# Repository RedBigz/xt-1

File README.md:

## IMPORTANT

- The JST PH connectors from the t-plugs to the supp. board need to have reverse connectors!

# XT-1

-green?style=for-the-badge)

A modular CoreXY 3D Printer with a focus on repairability.

| [READ THE JOURNAL](./JOURNAL.md) | [READ CAD CREDITS](CAD_CREDITS.md) |
| -------------------------------- | ---------------------------------- |

|  |                   |
| ---------------------------------------------------------------------- | ---------------------------------------------------------- |
|        |  |

## Who I am and why I made this

Hi, I'm May, a 15-year-old programmer and hardware enthusiast from Australia. I have spent the past few weeks developing a custom 3D printer based on the CoreXY motion system that allows for custom component bays to be inserted on the toolhead. I made this dovetail plug (t-plug) system to mimic the concept of [Framework](https://frame.work)'s laptop expansion bays. I believe expansion bays largely simplify repairs performed by consumers and allows for greater self-expression through custom designs that can be attached to the toolhead.

## What is this?

The XT-1 is a custom CoreXY 3D printer with two custom t-plug (as defined above) bays to transmit UART and 5V & 24V PWM signals for things such as:

- Accelerometers (not ADXL as they're SPI)
- Laser Diodes
- Fans

Here are some basic statistics for the printer:

- 2 t-plug bays
- 2WD CoreXY System
- 180x180x160 build volume
- ~360x360x420 external dimensions

# Gallery

## CAD Model

## Supplementary Board

## T-Plug

# Building

## CAD Models

To export parts, open the model in OnShape [here](https://cad.onshape.com/documents/9bd0c3164ed27c6437ee23ee/w/6070e846ece5dc4f933b41e5/e/3b4b9a8834f82e5e0afe2787) (I would suggest plugging in your computer before downloading, the models are hundreds of megs and just rendering them has crashed my desktop RX 7800XT over 10 times when rendering the full assembly)

To find the _assembly_ in .STEP format, check the `asm` folder in this repo.

## Wiring Diagram

## Quick BOM

**Quick Note:** This BOM is made largely for Hack Club's [Highway grant program](https://highway.hackclub.com) and prices reference the sale price I am able to purchase each product at (as @ 29/07/2025) in AUD (with a AUD -> USD exchange rate of $0.66 per A$1).

| Manufacturer           | Item                                                                    | Size                | Qty | Units | Unit Cost (AUD) | Cost (AUD) | Cost (USD) | Link                                                              |
| ---------------------- | ----------------------------------------------------------------------- | ------------------- | --- | ----- | --------------- | ---------- | ---------- | ----------------------------------------------------------------- |
| BIGTREETECH            | BTT SKR Mini E3 V3                                                      | -                   | 1   | each  | 52.51           | 52.51      | 34.66      | https://www.aliexpress.com/item/1005003519869375.html             |
| JINGLIN                | 5/lot 4-lead NEMA 17                                                    | -                   | 1   | lot   | 69.39           | 69.39      | 45.80      | https://www.aliexpress.com/item/1005008510880419.html             |
|                        | 2/lot 5015 Turbo Fan                                                    | -                   | 1   | lot   | 4.90            | 4.90       | 3.23       | https://www.aliexpress.com/item/32970914615.html                  |
| JINGLIN                | 2/lot 4020 Fan                                                          | -                   | 1   | lot   | 5.09            | 5.09       | 3.36       | https://www.aliexpress.com/item/32972111881.html                  |
| Ancufy                 | NEMA 14 + 1M cable                                                      | -                   | 1   | each  | 14.89           | 14.89      | 9.83       | https://www.aliexpress.com/item/1005006423228157.html             |
| HighQ                  | 2/lot 2020 V-Slot Extrusions                                            | 280mm               | 2   | lot   | 14.79           | 29.58      | 19.52      | https://www.aliexpress.com/item/1005007310271857.html             |
|                        |                                                                         | 320mm               | 2   | lot   | 15.89           | 31.78      | 20.97      |                                                                   |
|                        |                                                                         | 360mm               | 2   | lot   | 16.69           | 33.38      | 22.03      |                                                                   |
| Magic Dragon           | 2020 V-Slot Extrusions                                                  | 300mm               | 1   | each  | 8.47            | 8.47       | 5.59       | https://www.aliexpress.com/item/1005004679698586.html             |
|                        | MGN12 Linear Rail                                                       | 300mm               | 1   | each  | 20.39           | 20.39      | 13.46      | https://www.aliexpress.com/item/1005003696820721.html             |
| CHY CNC                | 2/lot 8mm Linear Shaft (M4x8mm)                                         | 200mm               | 2   | lot   | 16.29           | 32.58      | 21.50      | https://www.aliexpress.com/item/1005008854590053.html             |
| SNWNYN                 | 2x MGN12H rails, 4x MGN Blocks                                          | 200mm               | 1   | lot   | 34.59           | 34.59      | 22.83      | https://www.aliexpress.com/item/1005005966099152.html             |
| 3D ManufacturinG       | T8 Lead Screw + Nut                                                     | 200mm               | 3   | each  | 5.49            | 16.47      | 10.87      | https://www.aliexpress.com/item/1005007457419235.html             |
| ElectronicModule       | D20L25 Lead Screw Coupler                                               | -                   | 3   | each  | 2.76            | 8.28       | 5.46       | https://www.aliexpress.com/item/1005006456811778.html             |
| Haldis                 | Gearset Kit                                                             | -                   | 1   | each  | 21.39           | 21.39      | 14.12      | https://www.aliexpress.com/item/1005004699143725.html             |
| Lerdge                 | Lerdge iX 180mm Hotbed (Magnetic)                                       | -                   | 1   | each  | 30.79           | 30.79      | 20.32      | https://www.aliexpress.com/item/1005005641707683.html             |
| Good Luck Elec. Prod.  | 2/lot XL4015                                                            |                     | 1   | lot   | 6.21            | 6.21       | 4.10       | https://www.aliexpress.com/item/1005006823558141.html             |
| TLZWLA                 | 10/lot 01x08 2.54mm Female Header Socket                                | -                   | 1   | lot   | 2.16            | 2.16       | 1.43       | https://www.aliexpress.com/item/4001198421663.html                |
|                        | 10/lot 01x20 2.54mm Female Header Socket                                | -                   | 1   | lot   | 2.62            | 2.62       | 1.73       |                                                                   |
| Unnamed                | GY-291 ADXL345 Module                                                   | -                   | 1   | each  | 2.91            | 2.91       | 1.92       | https://www.aliexpress.com/item/1005007557329503.html             |
| ICGOGO                 | 40/lot F-F DuPont Jumper Wires                                          | 100mm               | 1   | lot   | 4.20            | 4.20       | 2.77       | https://www.aliexpress.com/item/1005002000655439.html             |
| YouKeyi                | 5/lot DRV8825 Module                                                    | -                   | 1   | lot   | 9.99            | 9.99       | 6.59       | https://www.aliexpress.com/item/1005009321177962.html             |
| USBO                   | IEC320 C14 Fused Switch                                                 | -                   | 1   | each  | 13.49           | 13.49      | 8.90       | https://www.aliexpress.com/item/4001315809458.html                |
| Wurth Elektronik       | 860040674004 100uF 50V                                                  | D8xL12mm            | 10  | each  | 0.555           | 5.55       | 3.66       | https://au.mouser.com/ProductDetail/Wurth-Elektronik/860040674004 |
| NINDEJIN NINDEJIN      | 50/lot M2x8mm Hex Wafer Head Screw                                      | -                   | 1   | lot   | 2.06            | 2.06       | 1.36       | https://www.aliexpress.com/item/1005008750192874.html             |
| Don Eden               | Pan Screws (PH)                                                         | 50pcs M3x5mm        | 1   | lot   | 2.82            | 2.82       | 1.86       | https://www.aliexpress.com/item/1005008709978631.html             |
|                        | (note, 16mm screws are in place of 15mm screws due to lack of listings) | 50pcs M3x16mm       | 1   | lot   | 4.29            | 4.29       | 2.83       |                                                                   |
|                        |                                                                         | 50pcs M3x35mm       | 1   | lot   | 6.09            | 6.09       | 4.02       |                                                                   |
|                        |                                                                         | 20pcs M4x8mm        | 1   | lot   | 3.32            | 3.32       | 2.19       |                                                                   |
|                        |                                                                         | 10pcs M5x8mm        | 7   | lot   | 3.32            | 23.24      | 15.34      |                                                                   |
|                        |                                                                         | 10pcs M5x16mm       | 2   | lot   | 3.90            | 7.80       | 5.15       |                                                                   |
|                        | Countersunk Screws                                                      | 20pcs M4x5mm        | 1   | lot   | 3.74            | 3.74       | 2.47       |                                                                   |
| Hundred Years          | Pan Screws (PH)                                                         | 50pcs M3x8mm        | 1   | lot   | 2.64            | 2.64       | 1.74       | https://www.aliexpress.com/item/1005006674754845.html             |
|                        |                                                                         | 50pcs M3x10mm       | 1   | lot   | 2.73            | 2.73       | 1.80       |                                                                   |
|                        |                                                                         | 50pcs M3x20mm       | 1   | lot   | 3.55            | 3.55       | 2.34       |                                                                   |
|                        |                                                                         | 50pcs M3x25mm       | 1   | lot   | 3.89            | 3.89       | 2.57       |                                                                   |
|                        |                                                                         | 50pcs M8x50mm       | 1   | lot   | 8.02            | 8.02       | 5.29       |                                                                   |
|                        | Heated Inserts                                                          | 100pcs M2L2 OD3.2mm | 1   | lot   | 2.89            | 2.89       | 1.91       | https://www.aliexpress.com/item/1005006967339727.html             |
|                        |                                                                         | 100pcs M3L4 OD4.2mm | 1   | lot   | 2.35            | 2.35       | 1.55       |                                                                   |
| CANOT                  | Hex Nuts                                                                | 50pcs M3            | 1   | lot   | 2.19            | 2.19       | 1.45       | https://www.aliexpress.com/item/1005007593861199.html             |
|                        |                                                                         | 10pcs M8            | 1   | lot   | 3.00            | 3.00       | 1.98       |                                                                   |
| RTLECS                 | 5/lot 8P 2.54mm Pogo Pins                                               | -                   | 1   | lot   | 11.59           | 11.59      | 7.65       | https://www.aliexpress.com/item/4001036140528.html                |
| MEAN WELL              | LRS-350-24                                                              | -                   | 1   | each  | 55.22           | 55.22      | 36.45      | https://au.mouser.com/ProductDetail/709-LRS350-24                 |
| FreeBoom               | PET Expandable Cable Sleeve                                             | 25mmx2m             | 1   | each  | 11.09           | 11.09      | 7.32       | https://www.aliexpress.com/item/1005009088606787.html             |
| Unnamed                | 100/lot M/F Spade Connectors                                            | 16-14AWG            | 1   | lot   | 5.61            | 5.61       | 3.70       | https://www.aliexpress.com/item/1005009138598203.html             |
| Unnamed                | Black Copper Cable                                                      | 5m, 22AWG           | 1   | lot   | 3.01            | 3.01       | 1.99       | https://www.aliexpress.com/item/1005006647928006.html             |
|                        |                                                                         | 2m, 16AWG           | 1   | lot   | 3.68            | 3.68       | 2.43       |                                                                   |
| PeoPoly                | Magneto X Lancer Melt Zone Long                                         | -                   | 1   | each  | 45.44           | 45.44      | 29.99      |                                                                   |
| Lerdge                 | PEI Bed                                                                 | 180x180             | 1   | each  | 11.79           | 11.79      | 7.78       | https://www.aliexpress.com/item/1005005332775787.html             |
| wuhushiyu              | T-Nuts                                                                  | M5 / 20 Series      | 150 | each  | 0.0676          | 10.14      | 6.69       | https://www.aliexpress.com/item/32814359094.html                  |
|                        |                                                                         | M3 / 20 Series      | 50  | each  | 0.0782          | 3.91       | 2.58       |                                                                   |
| Raspberry Pi           | Pi 4B (out of stock, cannot verify pricing details)                     | -                   | 1   | each  |                 | 0          | 0.00       |                                                                   |
|                        | Pi Pico H                                                               | -                   | 1   | each  | 8               | 8          | 5.28       | https://au.mouser.com/ProductDetail/Raspberry-Pi/SC0917           |
| WGXCPP                 | 127/lot Heat Shrink Kit                                                 | -                   | 1   | kit   | 4.09            | 4.09       | 2.70       | https://www.aliexpress.com/item/1005001787291963.html             |
| ?                      | microSD Card (self sourced)                                             | -                   | 2   | each  |                 | 0          | 0.00       |                                                                   |
| Tojiato                | 4/lot GT2 Idlers W6B5                                                   | 20T                 | 2   | lot   | 5.89            | 11.78      | 7.77       | https://www.aliexpress.com/item/1005007557987612.html             |
|                        |                                                                         | 20T Smooth          | 1   | lot   | 5.92            | 5.92       | 3.91       |                                                                   |
| Maecoom                | 3/lot GT2 Timing Pulley W6B5                                            | 20T                 | 1   | lot   | 6.55            | 6.55       | 4.32       | https://www.aliexpress.com/item/1005003176136280.html             |
| DFORCE Trianglelab     | 6mm Timing Belt                                                         | 3000mm              | 1   | each  | 19.11           | 19.11      | 12.61      | https://www.aliexpress.com/item/1005006507781085.html             |
| Panda Bearings         | 2/lot LM8UU Bearings                                                    | -                   | 2   | lot   | 3.73            | 7.46       | 4.92       | https://www.aliexpress.com/item/1005007070280422.html             |
| [PCB] (5/lot) {JLCPCB} | Supp. Board                                                             | -                   | 1   | lot   | 10.62           | 10.62      | 7.01       |                                                                   |
|                        | Male T-Plug                                                             | -                   | 1   | lot   | 3.21            | 3.21       | 2.12       |                                                                   |
|                        | Female T-Plug                                                           | -                   | 1   | lot   | 3.21            | 3.21       | 2.12       |                                                                   |
|                        | ADXL Connector                                                          | -                   | 1   | lot   | 3.21            | 3.21       | 2.12       |                                                                   |
| NEWHONGHUIDA Fastener  | 30/lot Dowel Pins                                                       | M5x20mm             | 1   | lot   | 7.38            | 7.38       | 4.87       | https://www.aliexpress.com/item/4000473863693.html                |
| excellence             | 20/lot JST PH2.0 8P Connector                                           | Horizontal          | 1   | lot   | 3.16            | 3.16       | 2.09       | https://www.aliexpress.com/item/1005007755047389.html             |
|                        |                                                                         | Vertical            | 1   | lot   | 3.10            | 3.10       | 2.05       |                                                                   |
| Unnamed                | 5/lot PH 8P Ribbon Connector (Single Head)                              | 800mm               | 2   | lot   | 8.39            | 16.78      | 11.07      | https://www.aliexpress.com/item/1005006460578382.html             |
| SVALID                 | 10/lot 4P 24AWG JST XH-2.54 Cable                                       | 150mm               | 1   | lot   | 4.19            | 4.19       | 2.77       | https://www.aliexpress.com/item/1005002376525415.html             |
| alinsin                | 10/lot KF120 2.54mm Terminal Block                                      | 4P                  | 1   | lot   | 4.42            | 4.42       | 2.92       | https://www.aliexpress.com/item/1005003179482974.html             |
|                        |                                                                         | 3P                  | 1   | lot   | 3.47            | 3.47       | 2.29       |                                                                   |
| Creality               | CR-Touch ABL (non-bracket)                                              | -                   | 1   | kit   | 38.79           | 38.79      | 25.60      | https://www.aliexpress.com/item/1005009104612536.html             |
| [Filament]             | 1kg PETG Black (self sourced)                                           |                     |     |       |                 | 0          | 0          |                                                                   |
|                        | 1kg PETG Pink (self sourced)                                            |                     |     |       |                 | 0          | 0          |                                                                   |
|                        |                                                                         |                     |     |       | Shipping        | 50.77      | 33.51      |                                                                   |
|                        |                                                                         |                     |     |       | Subtotal        | 922.93     | 609.13     |                                                                   |
|                        |                                                                         |                     |     |       | +10% GST        | 92.29      | 60.91      |                                                                   |
|                        |                                                                         |                     |     |       | Total           | 1015.22    | 670.05     |                                                                   |
|                        |                                                                         |                     |     |       | Hack Club Grant | 530.30     | 350.00     |                                                                   |
|                        |                                                                         |                     |     |       | Out Of Pocket   | 484.91     | 320.05     |                                                                   |

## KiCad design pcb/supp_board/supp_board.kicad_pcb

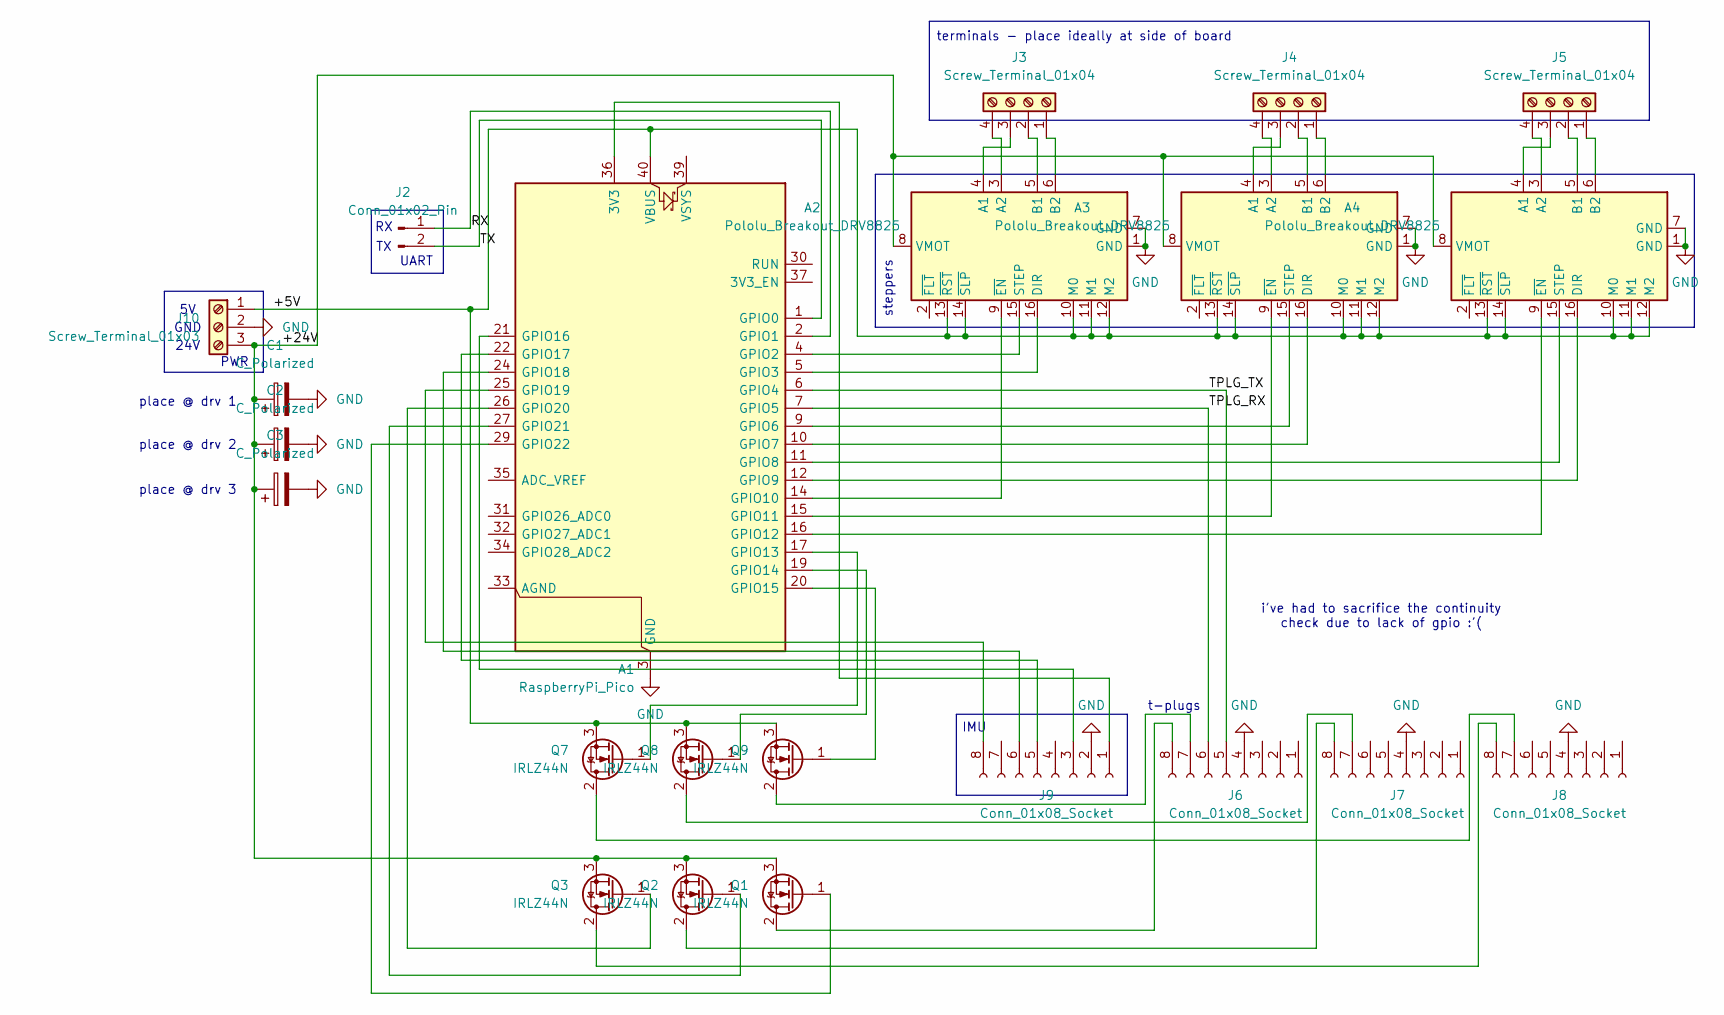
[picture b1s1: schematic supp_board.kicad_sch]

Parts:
A1: RaspberryPi_Pico; RaspberryPi_Pico_Common_THT
A2, A3, A4: Pololu_Breakout_DRV8825; Pololu_Breakout-16_15.2x20.3mm
C1, C2, C3: C_Polarized; CP_Radial_D8.0mm_P3.50mm
J2: Conn_01x02_Pin; SolderWire-0.5sqmm_1x02_P4.6mm_D0.9mm_OD2.1mm
J3, J4, J5: Screw_Terminal_01x04; TerminalBlock_MaiXu_MX126-5.0-04P_1x04_P5.00mm
J6, J7, J8, J9: Conn_01x08_Socket; JST_PH_B8B-PH-K_1x08_P2.00mm_Vertical
J10: Screw_Terminal_01x03; TerminalBlock_MaiXu_MX126-5.0-03P_1x03_P5.00mm
Q1, Q2, Q3, Q7, Q8, Q9: IRLZ44N; TO-220-3_Vertical

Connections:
/+5V: A1.40 (VBUS), A2.10 (M0), A2.11 (M1), A2.12 (M2), A2.13 (~RST), A2.14 (~SLP), A3.10 (M0), A3.11 (M1), A3.12 (M2), A3.13 (~RST), A3.14 (~SLP), A4.10 (M0), A4.11 (M1), A4.12 (M2), A4.13 (~RST), A4.14 (~SLP), J10.1, Q7.3 (S), Q8.3 (S), Q9.3 (S)
/+24V: A2.8 (VMOT), A3.8 (VMOT), A4.8 (VMOT), C1.1, C2.1, C3.1, J10.3, Q1.3 (S), Q2.3 (S), Q3.3 (S)
/RX: A1.2 (GPIO1), J2.1; also elsewhere on the board
/TPLG_RX: A1.7 (GPIO5), J6.6
/TPLG_TX: A1.6 (GPIO4), J6.5
/TX: A1.1 (GPIO0), J2.2; also elsewhere on the board
GND: A1.3 (GND), A1.8 (GND), A1.13 (GND), A1.18 (GND), A1.23 (GND), A1.28 (GND), A1.38 (GND), A2.1 (GND), A2.7 (GND), A3.1 (GND), A3.7 (GND), A4.1 (GND), A4.7 (GND), C1.2, C2.2, C3.2, J6.4, J7.4, J8.4, J9.2, J10.2
unnamed: A1.36 (3V3), J9.1
unnamed: A1.4 (GPIO2), A2.15 (STEP)
unnamed: A1.5 (GPIO3), A2.16 (DIR)
unnamed: A1.9 (GPIO6), A3.15 (STEP)
unnamed: A1.10 (GPIO7), A3.16 (DIR)
unnamed: A1.11 (GPIO8), A4.15 (STEP)
unnamed: A1.12 (GPIO9), A4.16 (DIR)
unnamed: A1.14 (GPIO10), A2.9 (~EN)
unnamed: A1.15 (GPIO11), A3.9 (~EN)
unnamed: A1.16 (GPIO12), A4.9 (~EN)
unnamed: A1.17 (GPIO13), Q7.1 (G)
unnamed: A1.19 (GPIO14), Q8.1 (G)
unnamed: A1.20 (GPIO15), Q9.1 (G)
unnamed: A1.21 (GPIO16), J9.3
unnamed: A1.22 (GPIO17), J9.5
unnamed: A1.24 (GPIO18), J9.6
unnamed: A1.25 (GPIO19), J9.8
unnamed: A1.26 (GPIO20), Q3.1 (G)
unnamed: A1.27 (GPIO21), Q2.1 (G)
unnamed: A1.29 (GPIO22), Q1.1 (G)
unnamed: A2.4 (A1), J3.3
unnamed: A2.3 (A2), J3.4
unnamed: A2.5 (B1), J3.2
unnamed: A2.6 (B2), J3.1
unnamed: A3.4 (A1), J4.3
unnamed: A3.3 (A2), J4.4
unnamed: A3.5 (B1), J4.2
unnamed: A3.6 (B2), J4.1
unnamed: A4.4 (A1), J5.3
unnamed: A4.3 (A2), J5.4
unnamed: A4.5 (B1), J5.2
unnamed: A4.6 (B2), J5.1
unnamed: J6.7, Q9.2 (D)
unnamed: J6.8, Q1.2 (D)
unnamed: J7.7, Q8.2 (D)
unnamed: J7.8, Q2.2 (D)
unnamed: J8.7, Q7.2 (D)
unnamed: J8.8, Q3.2 (D)

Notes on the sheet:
i've had to sacrifice the continuity check due to lack of gpio :'(
place @ drv 3
IMU
place @ drv 1
steppers
GND
place @ drv 2
PWR
24V
t-plugs
terminals - place ideally at side of board
UART

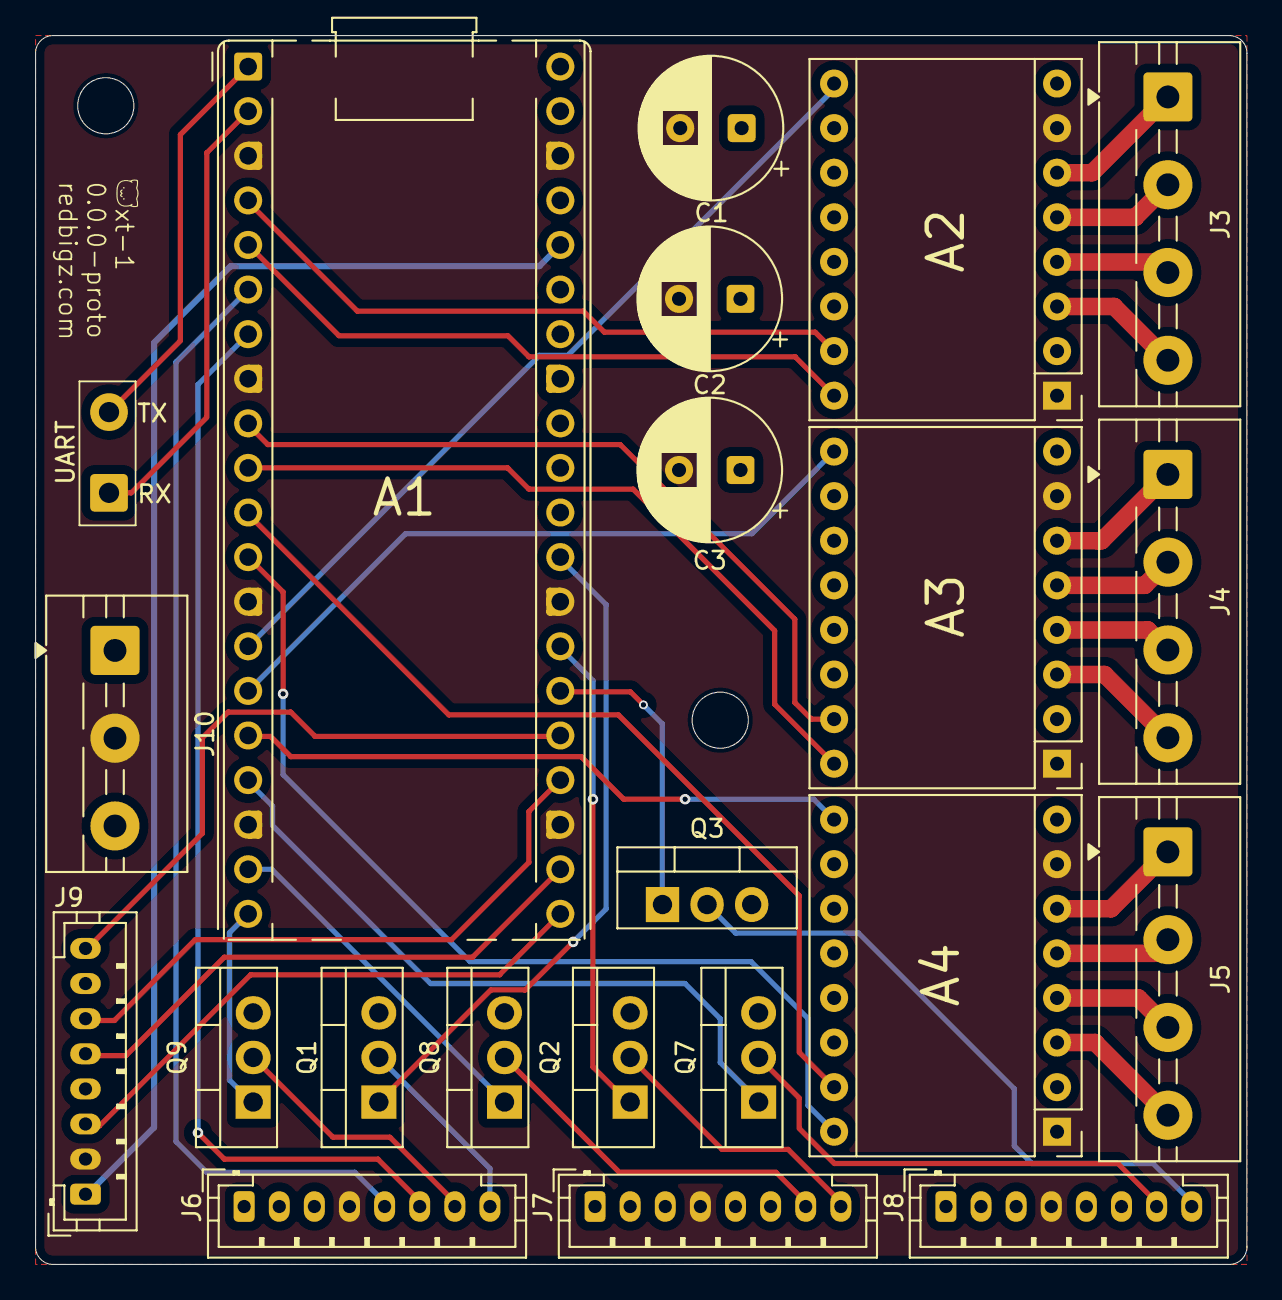
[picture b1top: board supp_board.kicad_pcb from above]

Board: 4 copper layers, 69.0 x 70.0 mm, 24 parts (0 on the bottom side), 45 nets.

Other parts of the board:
REF1, REF2: MountingHole_3.2mm_M3
UART: Conn_01x02_Pin; SolderWire-0.5sqmm_1x02_P4.6mm_D0.9mm_OD2.1mm

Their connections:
/RX: UART.1; also elsewhere on the board
/TX: UART.2; also elsewhere on the board

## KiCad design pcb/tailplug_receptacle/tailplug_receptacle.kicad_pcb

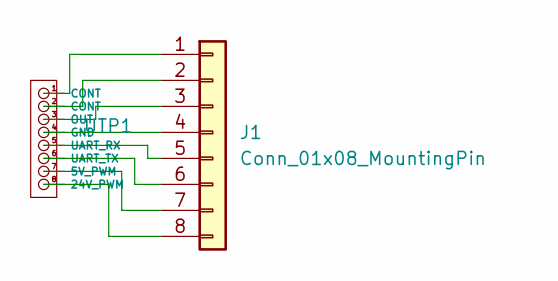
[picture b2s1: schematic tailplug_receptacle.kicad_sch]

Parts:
J1: Conn_01x08_MountingPin; JST_PH_S8B-PH-K_1x08_P2.00mm_Horizontal
UTP1: Tailplug_Female

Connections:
unnamed: J1.1, UTP1.1 (CONT)
unnamed: J1.2, UTP1.2 (CONT)
unnamed: J1.3, UTP1.3 (OUT)
unnamed: J1.4, UTP1.4 (GND)
unnamed: J1.5, UTP1.5 (UART_RX)
unnamed: J1.6, UTP1.6 (UART_TX)
unnamed: J1.7, UTP1.7 (5V_PWM)
unnamed: J1.8, UTP1.8 (24V_PWM)

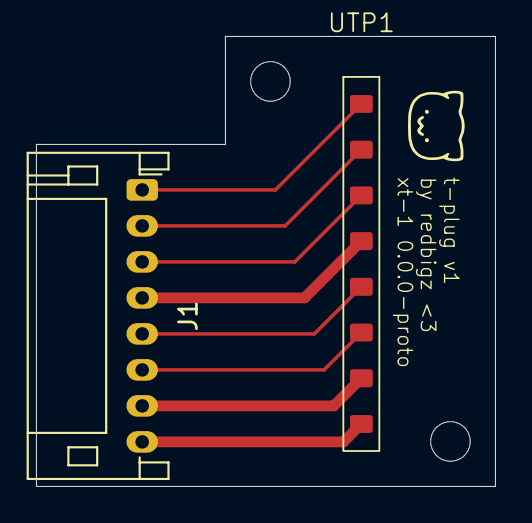
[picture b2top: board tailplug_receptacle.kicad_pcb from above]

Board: 2 copper layers, 25.5 x 25.0 mm, 4 parts (0 on the bottom side), 8 nets.

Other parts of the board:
REF1, REF2: MountingHole_2.2mm_M2

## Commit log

2025-07-15 Add log entry for research for the 15th
2025-07-17 Add 2025-07-16
2025-07-17 Add total time to journal
2025-07-17 Fix extra parens in ToC
2025-07-17 Add work from 2025-07-17
2025-07-17 Remove git submodule
2025-07-18 Add work from 2025-07-18
2025-07-19 Add work from 2025-07-19
2025-07-19 Added toolhead mount fix update, added checklist
2025-07-20 Add work from 2025-07-20
2025-07-20 Add cool README
2025-07-22 Add work from 2025-07-21
2025-07-23 Add work from 2025-07-22 to 2025-07-23
2025-07-23 Update the gallery
2025-07-26 Remove the scad folder
2025-07-26 Add CAD Credits
2025-07-26 Add PSU credit
2025-07-26 Add work from 2025-07-24 to 2025-07-26
2025-07-27 Add work from 2025-07-27
2025-07-29 Add work from 2025-07-28/29
2025-07-30 Add Pi Pico and Heat Shrink to BOM
2025-07-30 Round cents on BOM
2025-07-30 Propagate BOM to README
2025-07-30 Add new rendered images
2025-07-30 Reroute supp. board
2025-07-30 Change state to "Waiting for approval"
2025-07-30 Add supp. board image
2025-07-30 Replace boykissers on PCBs with my pfp (copyright reasons :3)
2025-07-31 Add Pi Pico link to BOM
2025-08-01 Fix total hours
    The total time was off by 4 hours (originally 100), but I recounted and found that it was 104 hours.
2025-08-02 Set stage to Approved
